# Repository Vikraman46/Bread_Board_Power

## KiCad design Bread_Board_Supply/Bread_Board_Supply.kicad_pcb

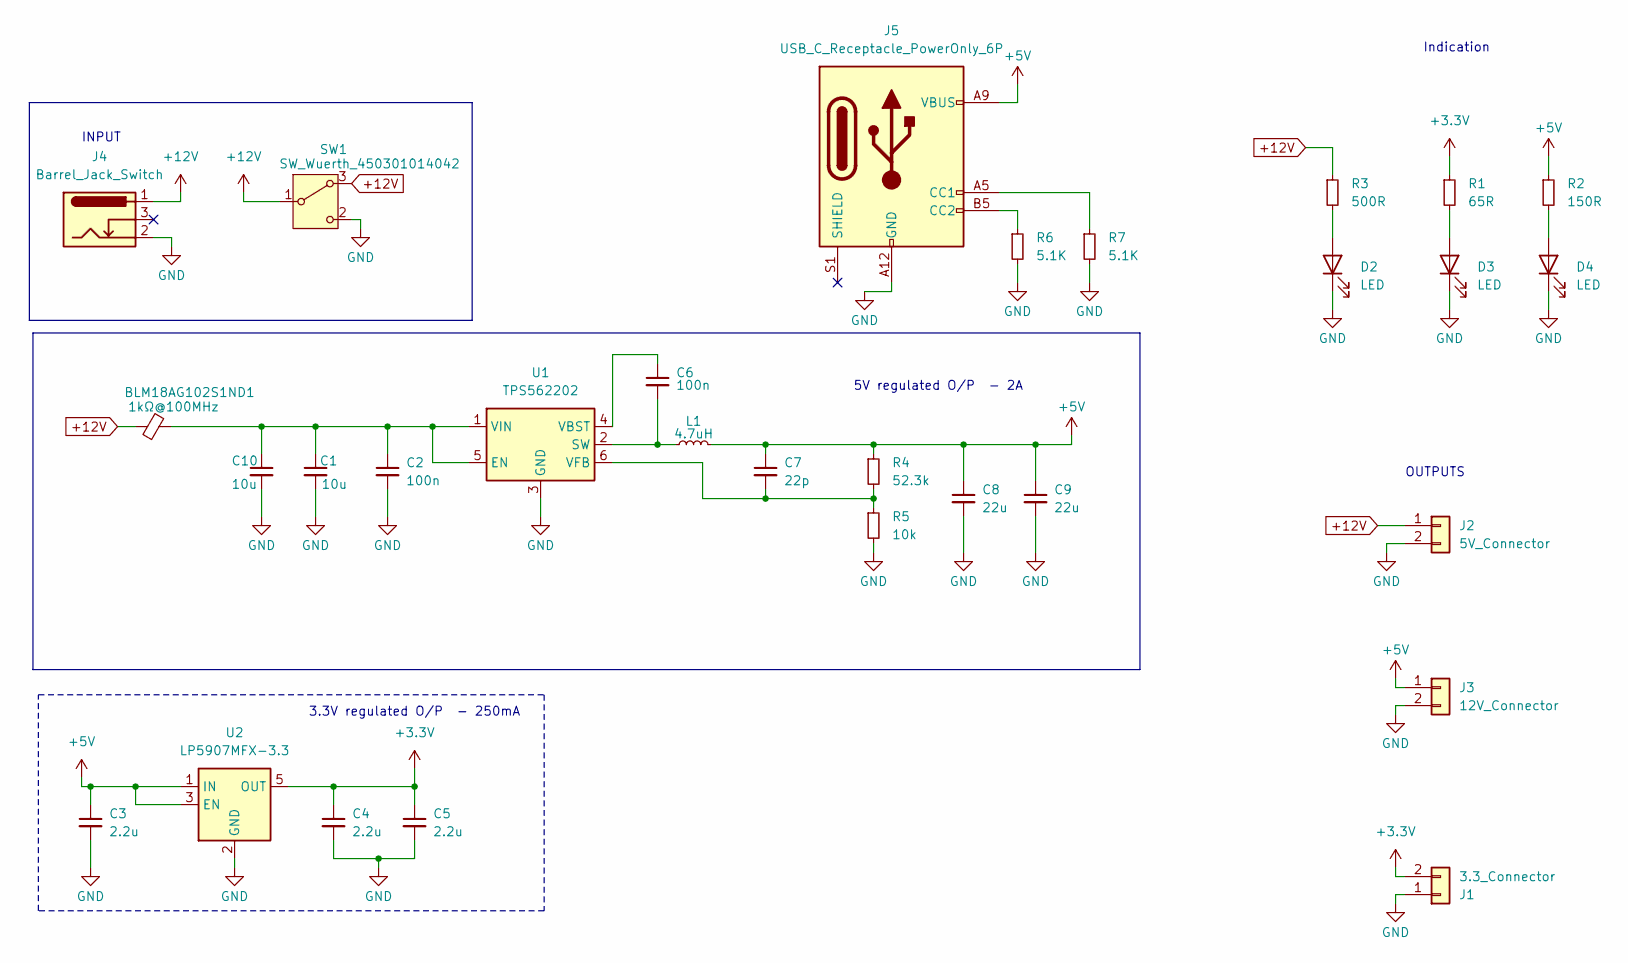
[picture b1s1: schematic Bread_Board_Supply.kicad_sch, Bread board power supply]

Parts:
BLM18AG102S1ND1: 1kΩ@100MHz; BLM18_MUR
C1, C10: 10u; WCAP-ATG5_5X11_DXL_
C2, C6: 100n; WCAP-ATG5_5X11_DXL_
C3, C4, C5: 2.2u; WCAP-ATG5_5X11_DXL_
C7: 22p; WCAP-ATG5_5X11_DXL_
C8, C9: 22u; WCAP-ATG5_5X11_DXL_
D2, D3, D4: LED; WL-TMRW_3MM
J1: 3.3_Connector; PinHeader_1x02_P1.00mm_Vertical
J2: 5V_Connector; PinHeader_1x02_P1.00mm_Vertical
J3: 12V_Connector; PinHeader_1x02_P1.00mm_Vertical
J4: Barrel_Jack_Switch; BarrelJack_Horizontal
J5: USB_C_Receptacle_PowerOnly_6P; USB_C_Receptacle_GCT_USB4125-xx-x_6P_TopMnt_Horizontal
L1: 4.7uH; IND_BWVS008_PUL
R1: 65R; ERL07_VIS
R2: 150R; ERL07_VIS
R3: 500R; ERL07_VIS
R4: 52.3k; ERL07_VIS
R5: 10k; ERL07_VIS
R6, R7: 5.1K; ERL07_VIS
SW1: SW_Wuerth_450301014042; SW_Slide-03_Wuerth-WS-SLTV_10x2.5x6.4_P2.54mm
U1: TPS562202; SOT-563
U2: LP5907MFX-3.3; SOT-23-5

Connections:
+3.3V: C4.1, C5.1, J1.2, R1.1, U2.5 (OUT)
+5V: C3.1, C7.1, C8.1, C9.1, J3.1, J5.A9 (VBUS), J5.B9 (VBUS), L1.2, R2.1, R4.1, U2.1 (IN), U2.3 (EN)
+12V: BLM18AG102S1ND1.1, J2.1, J4.1, R3.1, SW1.1 (B), SW1.3 (A)
GND: C1.2, C2.2, C3.2, C4.2, C5.2, C8.2, C9.2, C10.2, D2.1 (K), D3.1 (K), D4.1 (K), J1.1, J2.2, J3.2, J4.2, J5.A12 (GND), J5.B12 (GND), R5.2, R6.2, R7.2, SW1.2 (C), U1.3 (GND), U2.2 (GND)
unnamed: D2.2 (A), R3.2
unnamed: D3.2 (A), R1.2
unnamed: D4.2 (A), R2.2
unnamed: J5.A5 (CC1), R7.1
unnamed: J5.B5 (CC2), R6.1
unnamed: BLM18AG102S1ND1.2, C1.1, C2.1, C10.1, U1.1 (VIN), U1.5 (EN)
unnamed: C6.2, L1.1, U1.2 (SW)
unnamed: C6.1, U1.4 (VBST)
unnamed: C7.2, R4.2, R5.1, U1.6 (VFB)

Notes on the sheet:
5V regulated O/P - 2A
3.3V regulated O/P - 250mA
Indication
OUTPUTS
INPUT

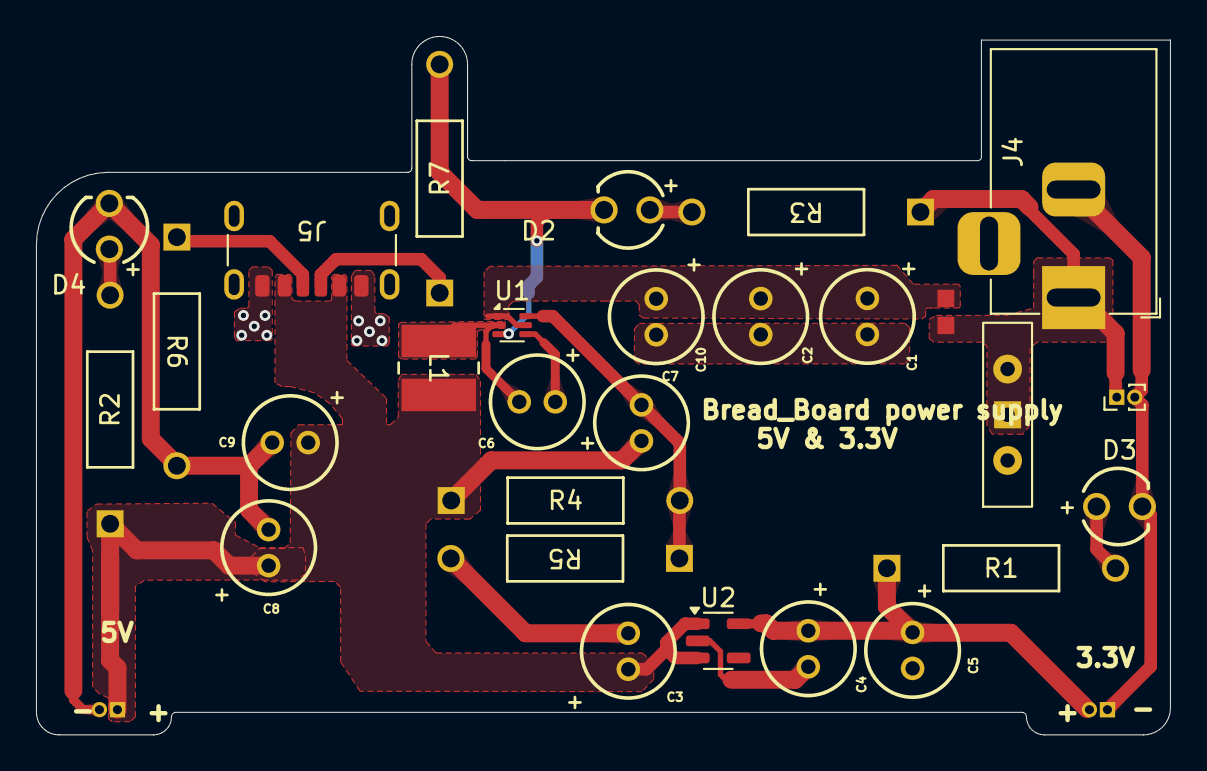
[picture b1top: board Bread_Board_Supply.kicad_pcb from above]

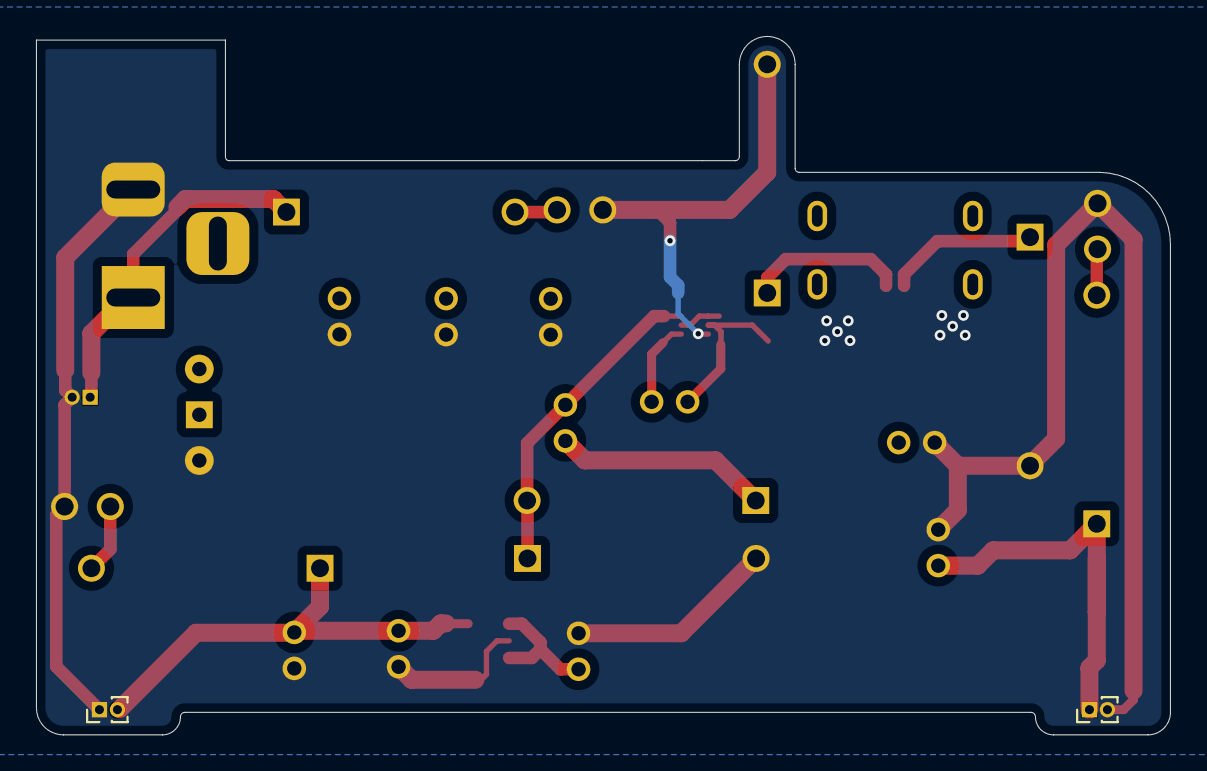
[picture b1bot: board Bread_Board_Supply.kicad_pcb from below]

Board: 2 copper layers, 63.0 x 38.8 mm, 30 parts (2 on the bottom side), 13 nets.

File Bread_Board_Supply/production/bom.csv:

Designator,Footprint,Quantity,Value,LCSC Part #
BLM18AG102S1ND1,BLM18_MUR,1,1kΩ@100MHz,
"C1, C10",WCAP-ATG5_5X11_DXL_,2,10u,
"C2, C6",WCAP-ATG5_5X11_DXL_,2,100n,
"C3, C4, C5",WCAP-ATG5_5X11_DXL_,3,2.2u,
C7,WCAP-ATG5_5X11_DXL_,1,22p,
"C8, C9",WCAP-ATG5_5X11_DXL_,2,22u,
"D2, D3, D4",WL-TMRW_3MM,3,LED,
J1,PinHeader_1x02_P1.00mm_Vertical,1,3.3_Connector,
J2,PinHeader_1x02_P1.00mm_Vertical,1,5V_Connector,
J3,PinHeader_1x02_P1.00mm_Vertical,1,12V_Connector,
J4,BarrelJack_Horizontal,1,Barrel_Jack_Switch,
L1,IND_BWVS008_PUL,1,4.7uH,
R1,ERL07_VIS,1,65R,
R2,ERL07_VIS,1,150R,
R3,ERL07_VIS,1,500R,
R4,ERL07_VIS,1,52.3k,
R5,ERL07_VIS,1,10k,
SW1,SW_Slide-03_Wuerth-WS-SLTV_10x2.5x6.4_P2.54mm,1,SW_Wuerth_450301014042,
U1,SOT-563,1,TPS562202,
U2,SOT-23-5,1,LP5907MFX-3.3,

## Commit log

2024-10-23 Layout Changes
2024-10-24 Layout finished
2024-10-25 USB C added
2024-10-26 ground routing
